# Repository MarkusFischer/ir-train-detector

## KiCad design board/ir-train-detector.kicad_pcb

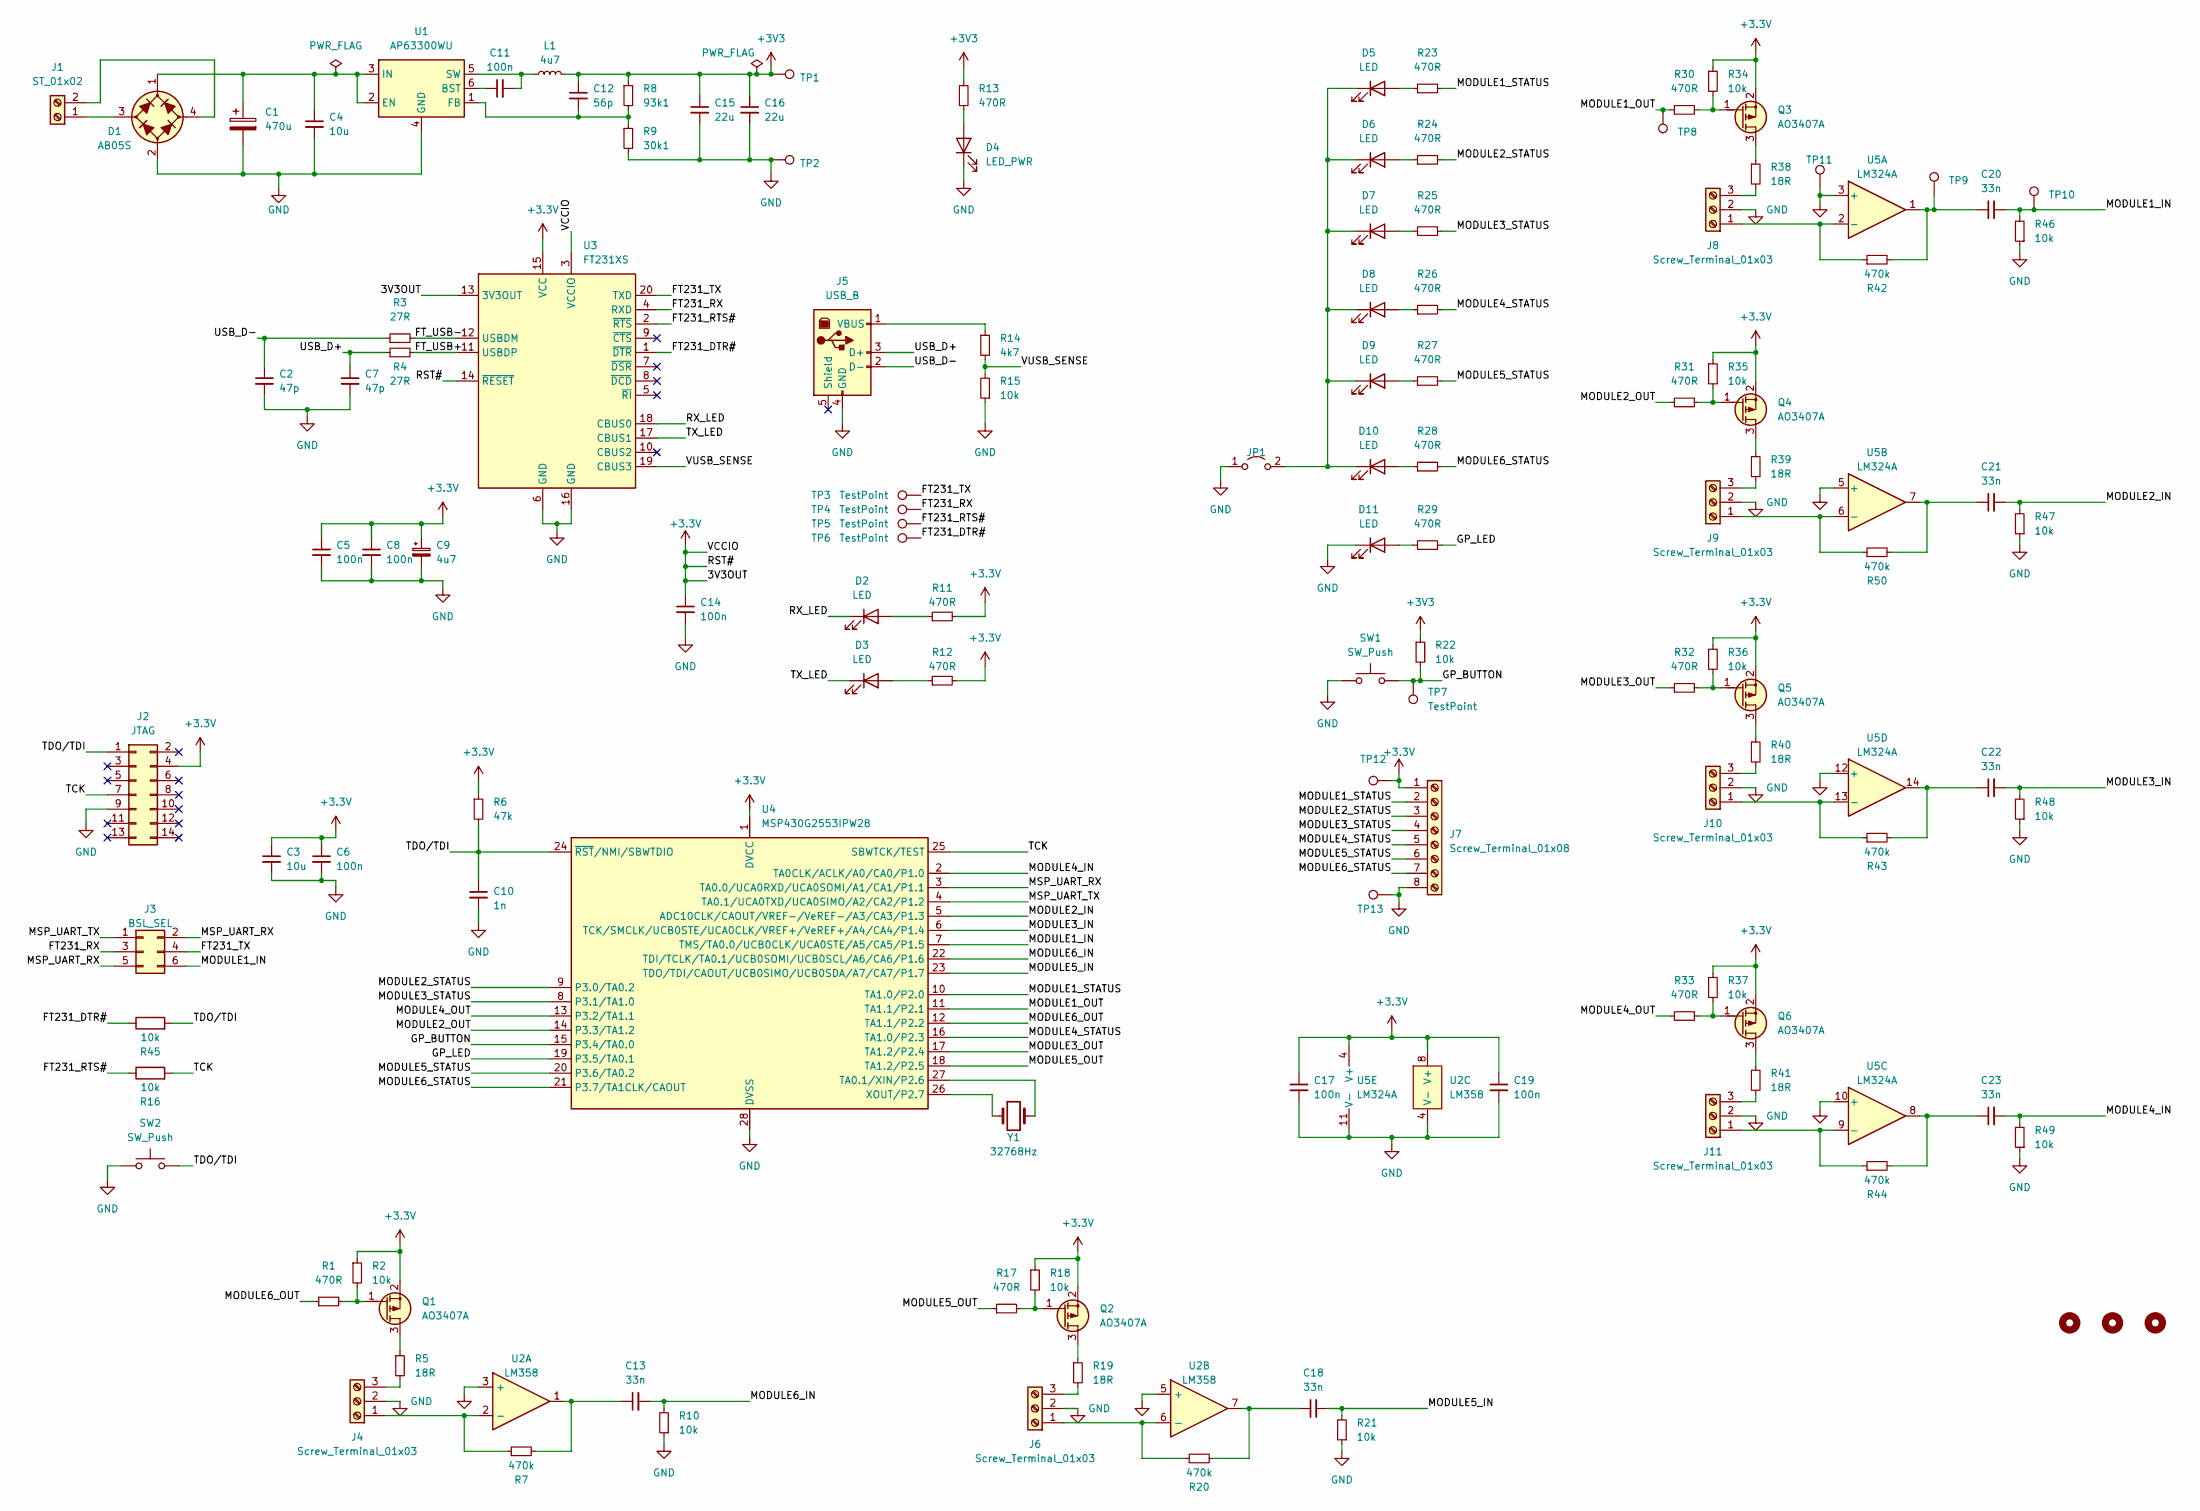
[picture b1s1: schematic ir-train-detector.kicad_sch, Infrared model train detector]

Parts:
C1: 470u; CP_Radial_D10.0mm_P5.00mm
C2, C7: 47p; C_0805_2012Metric
C3, C4: 10u; C_1206_3216Metric
C5, C6, C8, C11, C14, C17, C19: 100n; C_0603_1608Metric
C9: 4u7; CP_Radial_D4.0mm_P1.50mm
C10: 1n; C_0805_2012Metric
C12: 56p; C_0805_2012Metric
C13, C18, C20, C21, C22, C23: 33n; C_0603_1608Metric
C15, C16: 22u; C_1206_3216Metric
D1: AB05S; Diode_Bridge_Diotec_ABS
D2, D3, D5, D6, D7, D8, D9, D10, D11: LED; LED_0603_1608Metric_Pad1.05x0.95mm_HandSolder
D4: LED_PWR; LED_0603_1608Metric_Pad1.05x0.95mm_HandSolder
H1, H2, H3: MountingHole; MountingHole_3.2mm_M3_DIN965
J1: ST_01x02; TerminalBlock_RND_205-00001_1x02_P5.00mm_Horizontal
J2: JTAG; IDC-Header_2x07_P2.54mm_Vertical
J3: BSL_SEL; PinHeader_2x03_P2.54mm_Vertical
J4, J6, J8, J9, J10, J11: Screw_Terminal_01x03; TerminalBlock_RND_205-00013_1x03_P5.00mm_Horizontal
J5: USB_B; USB_B_Lumberg_2411_02_Horizontal
J7: Screw_Terminal_01x08; TerminalBlock_RND_205-00007_1x08_P5.00mm_Horizontal
JP1: Jumper_2_Open; JUMPER_SMD_1x2
L1: 4u7; L_Radial_D7.0mm_P3.00mm
Q1, Q2, Q3, Q4, Q5, Q6: AO3407A; SOT-23
R1, R11, R12, R13, R17, R23, R24, R25, R26, R27, R28, R29, R30, R31, R32, R33: 470R; R_0603_1608Metric_Pad1.05x0.95mm_HandSolder
R2, R10, R15, R16, R18, R21, R22, R34, R35, R36, R37, R45, R46, R47, R48, R49: 10k; R_0603_1608Metric_Pad1.05x0.95mm_HandSolder
R3, R4: 27R; R_0603_1608Metric_Pad1.05x0.95mm_HandSolder
R5, R19, R38, R39, R40, R41: 18R; R_1206_3216Metric_Pad1.42x1.75mm_HandSolder
R6: 47k; R_0603_1608Metric_Pad1.05x0.95mm_HandSolder
R7, R20, R42, R43, R44, R50: 470k; R_0603_1608Metric_Pad1.05x0.95mm_HandSolder
R8: 93k1; R_1206_3216Metric_Pad1.42x1.75mm_HandSolder
R9: 30k1; R_1206_3216Metric_Pad1.42x1.75mm_HandSolder
R14: 4k7; R_0603_1608Metric_Pad1.05x0.95mm_HandSolder
SW1, SW2: SW_Push; SW_PUSH_6mm
TP1, TP2, TP3, TP4, TP5, TP6, TP7, TP8, TP9, TP10, TP12, TP13: TestPoint; TestPoint_Pad_D1.5mm
TP11: TestPoint; TestPoint_Pad_1.5x1.5mm
U1: AP63300WU; TSOT-23-6_HandSoldering
U2: LM358; SOIC-8_3.9x4.9mm_P1.27mm; JLCPCB ID C7951
U3: FT231XS; SSOP-20_3.9x8.7mm_P0.635mm
U4: MSP430G2553IPW28; TSSOP-28_4.4x9.7mm_P0.65mm
U5: LM324A; SOIC-14_3.9x8.7mm_P1.27mm
Y1: 32768Hz; Crystal_C26-LF_D2.1mm_L6.5mm_Horizontal

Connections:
/FT231_DTR#: R45.1, TP6.1, U3.1 (~DTR)
/FT231_RTS#: R16.1, TP5.1, U3.2 (~RTS)
/FT231_RX: J3.3, TP4.1, U3.4 (RXD)
/FT231_TX: J3.4, TP3.1, U3.20 (TXD)
/FT_USB+: R4.2, U3.11 (USBDP)
/FT_USB-: R3.2, U3.12 (USBDM)
/GP_BUTTON: R22.2, SW1.2, TP7.1, U4.15 (P3.4/TA0.0)
/GP_LED: R29.2, U4.19 (P3.5/TA0.1)
/MODULE1_IN: C20.2, J3.6, R46.2, TP10.1, U4.7 (TMS/TA0.0/UCB0CLK/UCA0STE/A5/CA5/P1.5)
/MODULE1_OUT: R30.1, TP8.1, U4.11 (TA1.1/P2.1)
/MODULE1_STATUS: J7.2, R23.2, U4.10 (TA1.0/P2.0)
/MODULE2_IN: C21.2, R47.2, U4.5 (ADC10CLK/CAOUT/VREF-/VeREF-/A3/CA3/P1.3)
/MODULE2_OUT: R31.1, U4.14 (P3.3/TA1.2)
/MODULE2_STATUS: J7.3, R24.2, U4.9 (P3.0/TA0.2)
/MODULE3_IN: C22.2, R48.2, U4.6 (TCK/SMCLK/UCB0STE/UCA0CLK/VREF+/VeREF+/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)
/MODULE3_OUT: R32.1, U4.17 (TA1.2/P2.4)
/MODULE3_STATUS: J7.4, R25.2, U4.8 (P3.1/TA1.0)
/MODULE4_IN: C23.2, R49.2, U4.2 (TA0CLK/ACLK/A0/CA0/P1.0)
/MODULE4_OUT: R33.1, U4.13 (P3.2/TA1.1)
/MODULE4_STATUS: J7.5, R26.2, U4.16 (TA1.0/P2.3)
/MODULE5_IN: C18.2, R21.2, U4.23 (TDO/TDI/CAOUT/UCB0SIMO/UCB0SDA/A7/CA7/P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)
/MODULE5_OUT: R17.1, U4.18 (TA1.2/P2.5)
/MODULE5_STATUS: J7.6, R27.2, U4.20 (P3.6/TA0.2)
/MODULE6_IN: C13.2, R10.2, U4.22 (TDI/TCLK/TA0.1/UCB0SOMI/UCB0SCL/A6/CA6/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)
/MODULE6_OUT: R1.1, U4.12 (TA1.1/P2.2)
/MODULE6_STATUS: J7.7, R28.2, U4.21 (P3.7/TA1CLK/CAOUT)
/MSP_UART_RX: J3.2, J3.5, U4.3 (TA0.0/UCA0RXD/UCA0SOMI/A1/CA1/P1.1)
/MSP_UART_TX: J3.1, U4.4 (TA0.1/UCA0TXD/UCA0SIMO/A2/CA2/P1.2)
/RX_LED: D2.1 (K), U3.18 (CBUS0)
/TCK: J2.7, R16.2, U4.25 (SBWTCK/TEST)
/TDO/TDI: C10.1, J2.1, R6.2, R45.2, SW2.2, U4.24 (~RST/NMI/SBWTDIO)
/TX_LED: D3.1 (K), U3.17 (CBUS1)
/USB_D+: C7.1, J5.3 (D+), R4.1
/USB_D-: C2.1, J5.2 (D-), R3.1
/VUSB_SENSE: R14.2, R15.2, U3.19 (CBUS3)
GND: C1.2, C2.2, C3.2, C4.2, C5.2, C6.2, C7.2, C8.2, C9.2, C10.2, C14.2, C15.2, C16.2, C17.2, C19.2, D1.2 (-), D4.1 (K), D11.1 (K), J2.9, J4.2, J5.4 (GND), J6.2, J7.8, J8.2, J9.2, J10.2, J11.2, JP1.1 (A), R9.2, R10.1, R15.1, R21.1, R46.1, R47.1, R48.1, R49.1, SW1.1, SW2.1, TP2.1, TP11.1, TP13.1, U1.4 (GND), U2.3 (+), U2.4 (V-), U2.5 (+), U3.6 (GND), U3.16 (GND), U4.28 (DVSS), U5.3 (+), U5.5 (+), U5.10 (+), U5.11 (V-), U5.12 (+); also elsewhere on the board
unnamed: C1.1, C4.1, D1.1 (+), U1.2 (EN), U1.3 (IN)
unnamed: C13.1, R7.2, U2.1
unnamed: C18.1, R20.2, U2.7
unnamed: C20.1, R42.2, TP9.1, U5.1
unnamed: C21.1, R50.2, U5.7
unnamed: C22.1, R43.2, U5.14
unnamed: C23.1, R44.2, U5.8
unnamed: D1.3 (1), J1.1
unnamed: D1.4 (2), J1.2
unnamed: D2.2 (A), R11.1
unnamed: D3.2 (A), R12.1
unnamed: D4.2 (A), R13.2
unnamed: D5.2 (A), R23.1
unnamed: D6.2 (A), R24.1
unnamed: D7.2 (A), R25.1
unnamed: D8.2 (A), R26.1
unnamed: D9.2 (A), R27.1
unnamed: D10.2 (A), R28.1
unnamed: D5.1 (K), D6.1 (K), D7.1 (K), D8.1 (K), D9.1 (K), D10.1 (K), JP1.2 (B)
unnamed: D11.2 (A), R29.1
unnamed: J4.1, R7.1, U2.2 (-)
unnamed: J4.3, R5.2
unnamed: J5.1 (VBUS), R14.1
unnamed: J6.1, R20.1, U2.6 (-)
unnamed: J6.3, R19.2
unnamed: J8.1, R42.1, U5.2 (-)
unnamed: J8.3, R38.2
unnamed: J9.1, R50.1, U5.6 (-)
unnamed: J9.3, R39.2
unnamed: J10.1, R43.1, U5.13 (-)
unnamed: J10.3, R40.2
unnamed: J11.1, R44.1, U5.9 (-)
unnamed: J11.3, R41.2
unnamed: Q1.3 (D), R5.1
unnamed: Q1.1 (G), R1.2, R2.2
unnamed: Q2.3 (D), R19.1
unnamed: Q2.1 (G), R17.2, R18.2
unnamed: Q3.3 (D), R38.1
unnamed: Q3.1 (G), R30.2, R34.2
unnamed: Q4.3 (D), R39.1
unnamed: Q4.1 (G), R31.2, R35.2
unnamed: Q5.3 (D), R40.1
unnamed: Q5.1 (G), R32.2, R36.2
unnamed: Q6.3 (D), R41.1
unnamed: Q6.1 (G), R33.2, R37.2
unnamed: C11.1, U1.6 (BST)
unnamed: C12.2, R8.2, R9.1, U1.1 (FB)
unnamed: C11.2, L1.1, U1.5 (SW)
unnamed: U4.27 (TA0.1/XIN/P2.6), Y1.1
unnamed: U4.26 (XOUT/P2.7), Y1.2

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
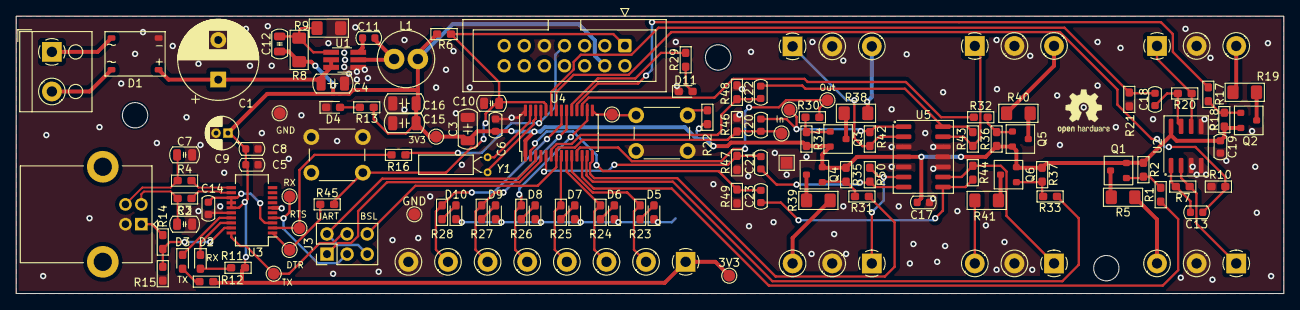
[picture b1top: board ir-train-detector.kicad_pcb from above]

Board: 2 copper layers, 160.0 x 35.0 mm, 127 parts (1 on the bottom side), 87 nets.

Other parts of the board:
3V3: TestPoint; TestPoint_Pad_D1.5mm
GND: TestPoint; TestPoint_Pad_D1.5mm

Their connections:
GND: GND.1; also elsewhere on the board

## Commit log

2022-12-29 starting to design hardware
2023-01-18 power section schematic finished
2023-01-21 added usb interface
2023-01-22 first draft of final schematic
2023-01-22 pdf schematic
2023-01-24 added footprints
2023-01-25 finished schematic
2023-01-26 board layout
2023-01-26 finished board
2023-01-27 finished hardware revision 1.0
2023-02-06 production hw rev 1.0
2023-02-07 project setup
2023-02-08 simple test program
2023-02-08 added template for ftdi231x
2023-02-13 ft231x config
2023-03-12 output signal creation
2023-03-15 some debugging code
2023-03-22 finished hardware rev 1.1
2023-05-09 single channel works
2023-05-09 code cleanup
2023-05-09 moved modules for better name structure
2023-05-09 statuse led manager to allow multiple channels
2023-05-10 rough usage of uart
2023-06-25 uart interrupts working; design of commands
2023-09-10 rework of uart commands
2023-09-10 updated uart command set
2023-09-10 use fixed sized status manager
2023-09-10 first implementation of uart commands
2023-09-10 controller does answer successful
2023-09-16 ring buffered queue for uart
2023-09-16 std::lock_guard like wrapper to disable (and reenable) interrupts
2023-09-16 removed local variables
2023-09-16 fixed uart errors
2023-09-17 unfinished configuration store
2023-09-17 using configuration storage
2023-09-17 working flash configuration storage
2023-09-17 implemented write protection
2023-09-20 Multi channel implementation with fixed gate time
2023-09-21 fixed multi channel mode
2023-09-21 updated hal
2023-09-21 basic configuration
2023-09-22 try to fix faulty uart
2023-09-22 finished firmware
2023-09-23 implemented energy savings
2023-09-23 using low power modes
2024-04-30 msp430hal update
